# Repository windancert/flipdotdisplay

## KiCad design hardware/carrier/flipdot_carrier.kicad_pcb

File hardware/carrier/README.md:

# Flipdot S3 Pico driver, rev A

A two-layer board that replaces the breadboard: it holds the Waveshare ESP32-S3-Pico in
sockets, the two ribbon headers, the 10k pull-downs, the 20 V / 5 V power stage and a
0.1 ohm resistor for measuring the coil current on a scope. The
circuit is the bench wiring from `firmware/README.md` plus the module power plan in
`CLAUDE.md`, so the firmware does not change. Everything is through-hole and can be
soldered by hand. Board size 111 x 85 mm, four M3 holes.

Layout: ribbon B (COL-SEL4-7) on the left edge and ribbon A (COL-SEL0-3) on the right,
matching where each chain starts on the display: the top row's chain starts at its left
end, and the bottom row is rotated, so its chain starts at the right end. The S3 Pico sits
upright in the middle, USB towards the top edge, antenna at the bottom edge pointing away
from the panels. The pull-downs are between the left header and the S3 Pico, the power stage
below the shared lines on the right, with the 20 V screw terminal on the bottom edge.

Status: designed and checked by KiCad (ERC and DRC clean, the board matches the
schematic), **not yet ordered or built**.

## Files

| File | What |
|------|------|
| `flipdot_carrier.kicad_pro` | open this in KiCad 10 |
| `flipdot_carrier.kicad_sch` | schematic |
| `flipdot_carrier.kicad_pcb` | board, placed and routed |
| `flipdot_carrier_schematic.pdf`, `flipdot_carrier_layout.pdf` | for viewing without KiCad |
| `flipdot_carrier_gerbers.zip` | the file a board maker needs |
| `flipdot.kicad_sym` | project symbols: the ESP32-S3-Pico and a +20V power symbol |
| `tools/` | the generator that makes all of the above (see the end) |

## Parts

| Ref | Qty | Part | Notes |
|-----|-----|------|-------|
| U1 | 1 | Waveshare ESP32-S3-Pico | plugs in, not soldered |
| - | 2 | 1x20 female header, 2.54 mm | the S3 Pico's socket |
| - | 2 | 1x20 male pin header, 2.54 mm | soldered to the S3 Pico, if it has none |
| J1, J2 | 2 | 2x13 shrouded box header, 2.54 mm, straight | ribbon A (COL-SEL0-3), ribbon B (COL-SEL4-7) |
| J3 | 1 | 2-pole screw terminal, 5.08 mm pitch | 20 V in, from the PD trigger module |
| U2 | 1 | Recom R-78E5.0-1.0 | 5 V buck, SIP-3 |
| D1 | 1 | P6KE30CA, DO-15 (Reichelt P6KE 30CA) | bidirectional TVS, 25.6 V standoff, clamps ~41 V; fits either way round |
| D2, D3 | 2 | 1N5819, DO-41 | Schottky; replace the SS34 and SS14 of the module plan |
| C1 | 1 | 470 uF, 35 V or higher, radial, 12.5 mm max diameter, 5 mm lead spacing | coil rail bulk |
| C2 | 1 | 4.7 uF, 50 V, radial, 5 mm diameter, 2 mm lead spacing | buck input |
| C3 | 1 | 100 uF, 16 V, radial, 6.3 mm diameter, 2.5 mm lead spacing | buck output (keep under 220 uF) |
| C4, C5 | 2 | 100 nF ceramic, 5 mm lead spacing | 3.3 V decoupling at each ribbon header |
| R1-R10 | 10 | 10k, 1/4 W | pull-downs: R1-R8 on COL-SEL0-7, R9 ROW-HIGH, R10 ROW-LOW |
| R11 | 1 | 0.1 ohm, 10%, 2 W wirewound, Vitrohm BW235 (Reichelt 2W DRAHT 0,1), body 14.3 x 5.7 mm, 20.32 mm lead spacing | coil current sense; a wire link if not wanted |
| TP1-TP15 | 15 | Keystone 5000-series miniature test point: 3x 5000 red, 2x 5001 black, 4x 5003 orange, 6x 5004 yellow | suggested: red 20V/I+/I-, black GND, orange VIN/5V/VSYS/3V3, yellow signals |
| - | 1 | Joy-IT COM-ZY12PDN-ST (Reichelt DEBO USB-PD 1) | off the board, two wires to J3 |

## Before ordering

1. **S3 Pico row spacing.** Confirmed: the Waveshare board's pin rows measure 17.8 mm
   apart, matching the Raspberry Pi Pico footprint (17.78 mm), pin 1 next to USB.
2. **Antenna end.** Confirmed: the S3 Pico's antenna is on the short edge opposite USB,
   between the pins for GPIO39/40 and GPIO41/42. That end sits at the board's bottom
   edge (marked ANTENNA END). From the GPIO38 pin down to the board edge, across the
   S3 Pico's width plus a margin, there is no ground fill and no vias on either layer; the
   only copper is the four signal pins there and the tracks that reach them from the
   sides. The S3 Pico's GND pin 18 is left unconnected for the same reason.
3. **Ribbon pin 1.** The triangle on the silkscreen next to each header marks pin 1.
   Pin 1 is GND, pin 26 is 20 V. With the ribbons crimped as on the bench (pin 1 to
   pin 1), the red stripe goes on the triangle side.

## Test points

Labelled loops for a meter probe or a scope clip:

| Where | Test points |
|-------|-------------|
| top edge, left of the USB plug | R-HI, R-LO (the two strobes), ROW4, COL4 (top address bits), SEL0, SEL4 (first panel on each ribbon) |
| top edge, right of the USB plug | 3V3, GND |
| power corner, bottom right | 20V, VIN, 5V, VSYS, GND, top to bottom in the order the power flows |
| above R11, which sits above D1 | I+, I- (coil current) |

VIN is the buck's input, behind D2. If 5V reads 0 V with 20V present, VIN tells the
cases apart: about 0 V means D2 is in backwards or C2 is shorted; about 19.5 V means
the R-78E itself.

The strobes are the ones to watch on a scope: each pulse should be about 260 us, never
more than the firmware's 400 us ceiling.

**Coil current.** The coils get their 20 V through R11 (0.1 ohm), which sits behind C1 so
it carries the pulses themselves. Probe I+ on one channel and I- on another, both ground
clips on GND, both channels AC-coupled at about 20 mV/div, and show CH1 - CH2: 100 mV is
1 A, so a 0.74 A pulse reads about 74 mV. Trigger on R-HI or R-LO with a third channel.
R11 takes about 0.6 % off the coil current (0.1 ohm against the coil's 16 ohm).

I+ is tapped straight off R11's pad. Ribbon A's current also leaves R11 straight from its
pad, but ribbon B's runs past the I- test point first, through about 4.5 mm of track, so
pulses on the top row (ribbon B) read about 3 % high.

R11 is only good to 10 %, so measure its real value once, before the S3 Pico goes in and
with no ribbons connected: set the bench supply to about 1 V with a 0.5 A current limit,
connect + to I- and - to I+ (at that voltage the current can only flow through R11),
read the current on the supply and the millivolts between I+ and I- on a multimeter, and
divide. Use that value instead of 0.1 ohm when converting scope readings to amps.

## Ordering

Planned maker: **Aisler** (Germany), 2-layer standard boards. Aisler reads KiCad files
directly: upload `flipdot_carrier.kicad_pcb` (or `flipdot_carrier_gerbers.zip`) and check
its preview of both sides. The tightest rules used are 0.2 mm clearance, 0.3 mm tracks
and 0.3 mm via holes, within every maker's standard process. Parts from Reichelt.

Order only after the 20 V charger test (see CLAUDE.md, Power): if the charger does not
settle on 20 V with ~490 uF on the module's output, the board needs a coil-rail switch.
**Result: it depends on the charger.** One charger failed about half the time with
470 uF directly on the module's output, another passed every time (see CLAUDE.md).
**Open item:** the switched coil rail (version 2 of the power page) is postponed, not
dropped; this board has no switch yet. Decide before ordering.

## Assembly

Solder the lowest parts first so the board lies flat on the bench:

1. R1-R10 (either way round).
2. D2, D3: the band is the cathode, the silkscreen marks it with a K. D1 (bidirectional)
   goes either way round.
3. C4, C5 (either way round), R11 (either way round), and the 15 test point loops
   TP1-TP15 (either way round; the colours suggested in the parts list).
4. The two 1x20 female headers for the S3 Pico. Plug the S3 Pico into them first so they line
   up, then solder.
5. J1, J2: the notch in the shroud goes on the side the silkscreen outline shows.
6. C1, C2, C3: the long leg is +, the stripe on the can is -, the silkscreen marks +.
7. U2: pin 1 (+Vin, marked on the module) in the leftmost hole, the body over its
   silkscreen outline.
8. J3: the wire openings face the bottom edge.

## First power-up

With the S3 Pico **out** of its socket and no ribbons connected:

1. Set the PD trigger to 20 V (LED dark blue) and connect it to J3: + on the left,
   - on the right, as marked.
2. Measure against a GND test point:
   - 20V test point, J1 pin 26 and J2 pin 26: about 20 V.
   - VIN test point: about 19.5 V (20 V minus D2).
   - 5V test point: about 5 V.
   - VSYS test point (also socket pin 39, right-hand row, second from the top):
     about 4.7 V (5 V minus the diode). **If this reads 20 V, stop.**
   - Every other socket pin: 0 V.
3. Unplug, insert the S3 Pico (USB towards the top edge), power up again. The
   status LED should go blue, then yellow and green as on the bench. The 3V3 test
   point should now read about 3.3 V.
4. Unpower, then connect one ribbon between the board and a panel and check its
   orientation with a continuity meter, still unpowered: J3 - to the panel's ground
   plane (or its ribbon pin 1 or 2) must beep, J3 + to the panel's ground must not.
   A plug the wrong way round puts 20 V on the panel's ground pins. Repeat for the
   other ribbon, then power up.

## Regenerating

The schematic and board are generated by `tools/` and can be rebuilt with:

```sh
python tools/build.py
```

It needs KiCad 10 installed at its default path. It regenerates the schematic, runs ERC,
places and routes the board (about a minute and a half), runs DRC, and writes the
Gerbers and PDFs.

- `tools/design.py` holds the parts, their connections and their positions on the board.
- `tools/gen_sch.py` writes the schematic, `tools/gen_pcb.py` the board, using
  `tools/router.py`, a small autorouter.
- `tools/render.py out.png` draws the copper to a PNG for a quick look.

A rebuild overwrites the `.kicad_pcb`. To edit the board by hand in KiCad, do that from
then on and stop using `build.py` for the board; `python tools/build.py --no-pcb` still
rebuilds only the schematic.

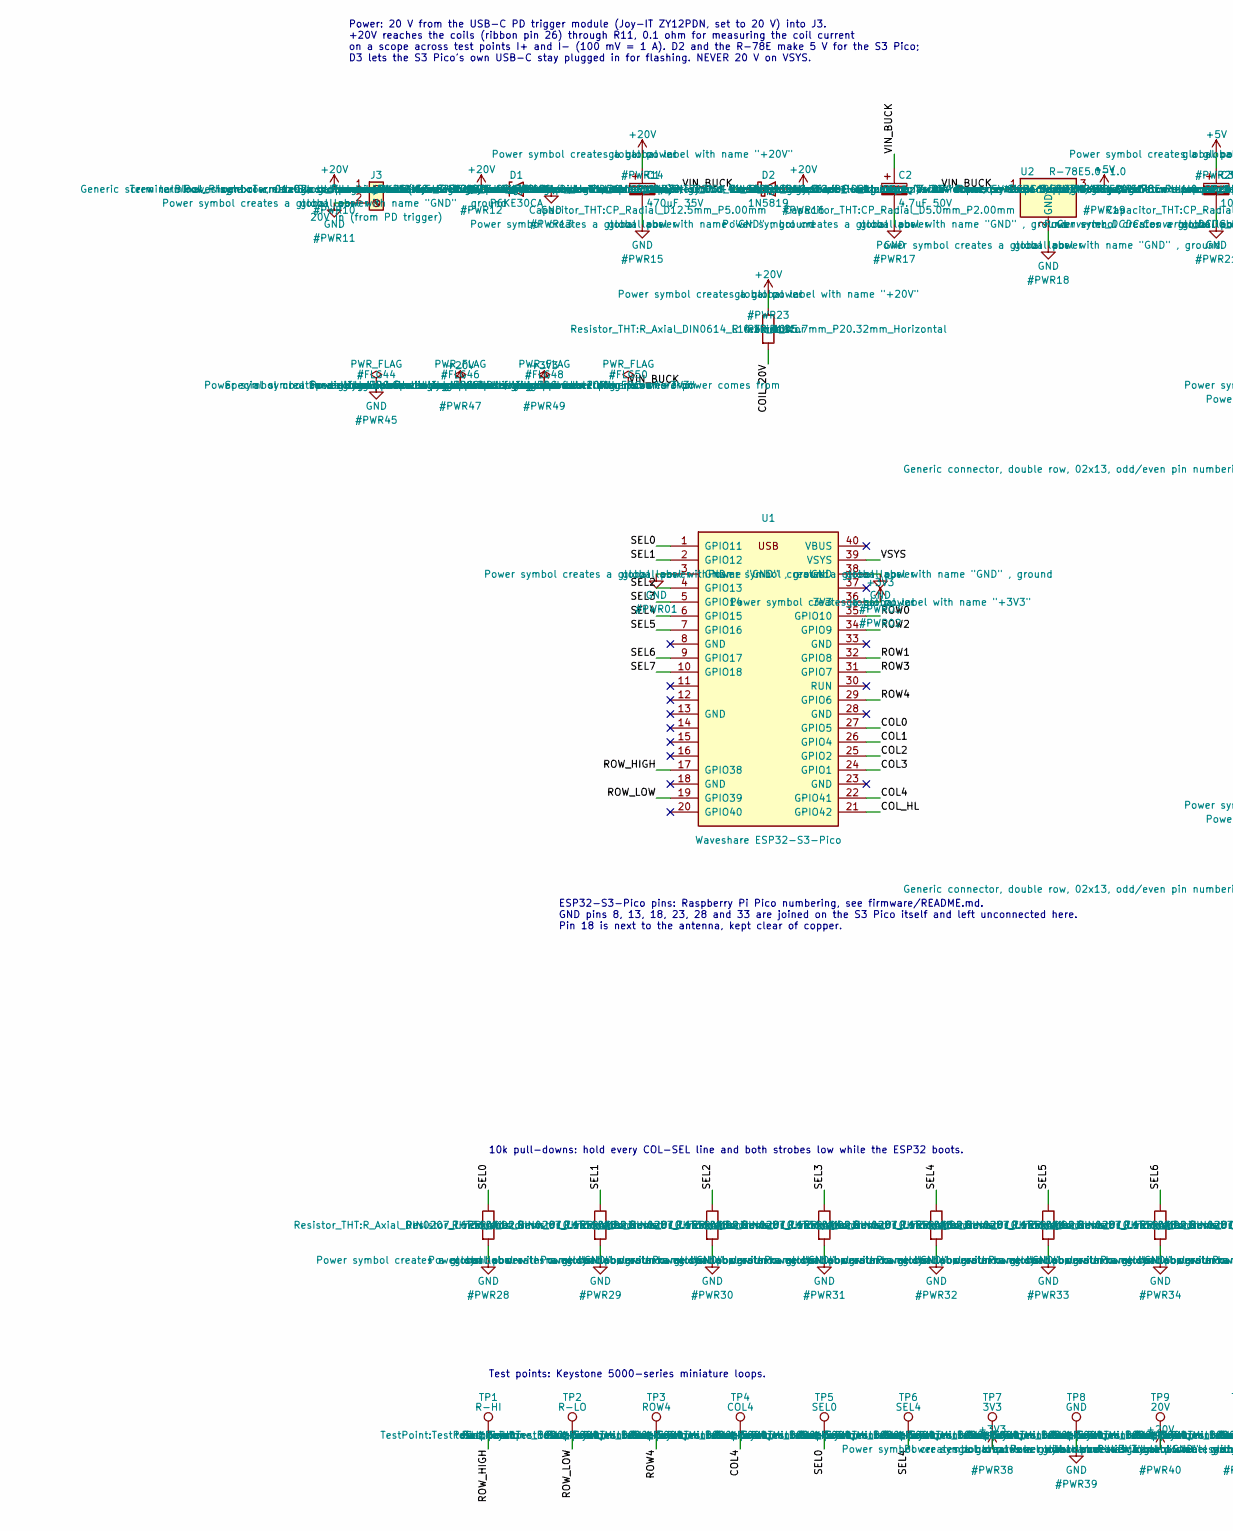
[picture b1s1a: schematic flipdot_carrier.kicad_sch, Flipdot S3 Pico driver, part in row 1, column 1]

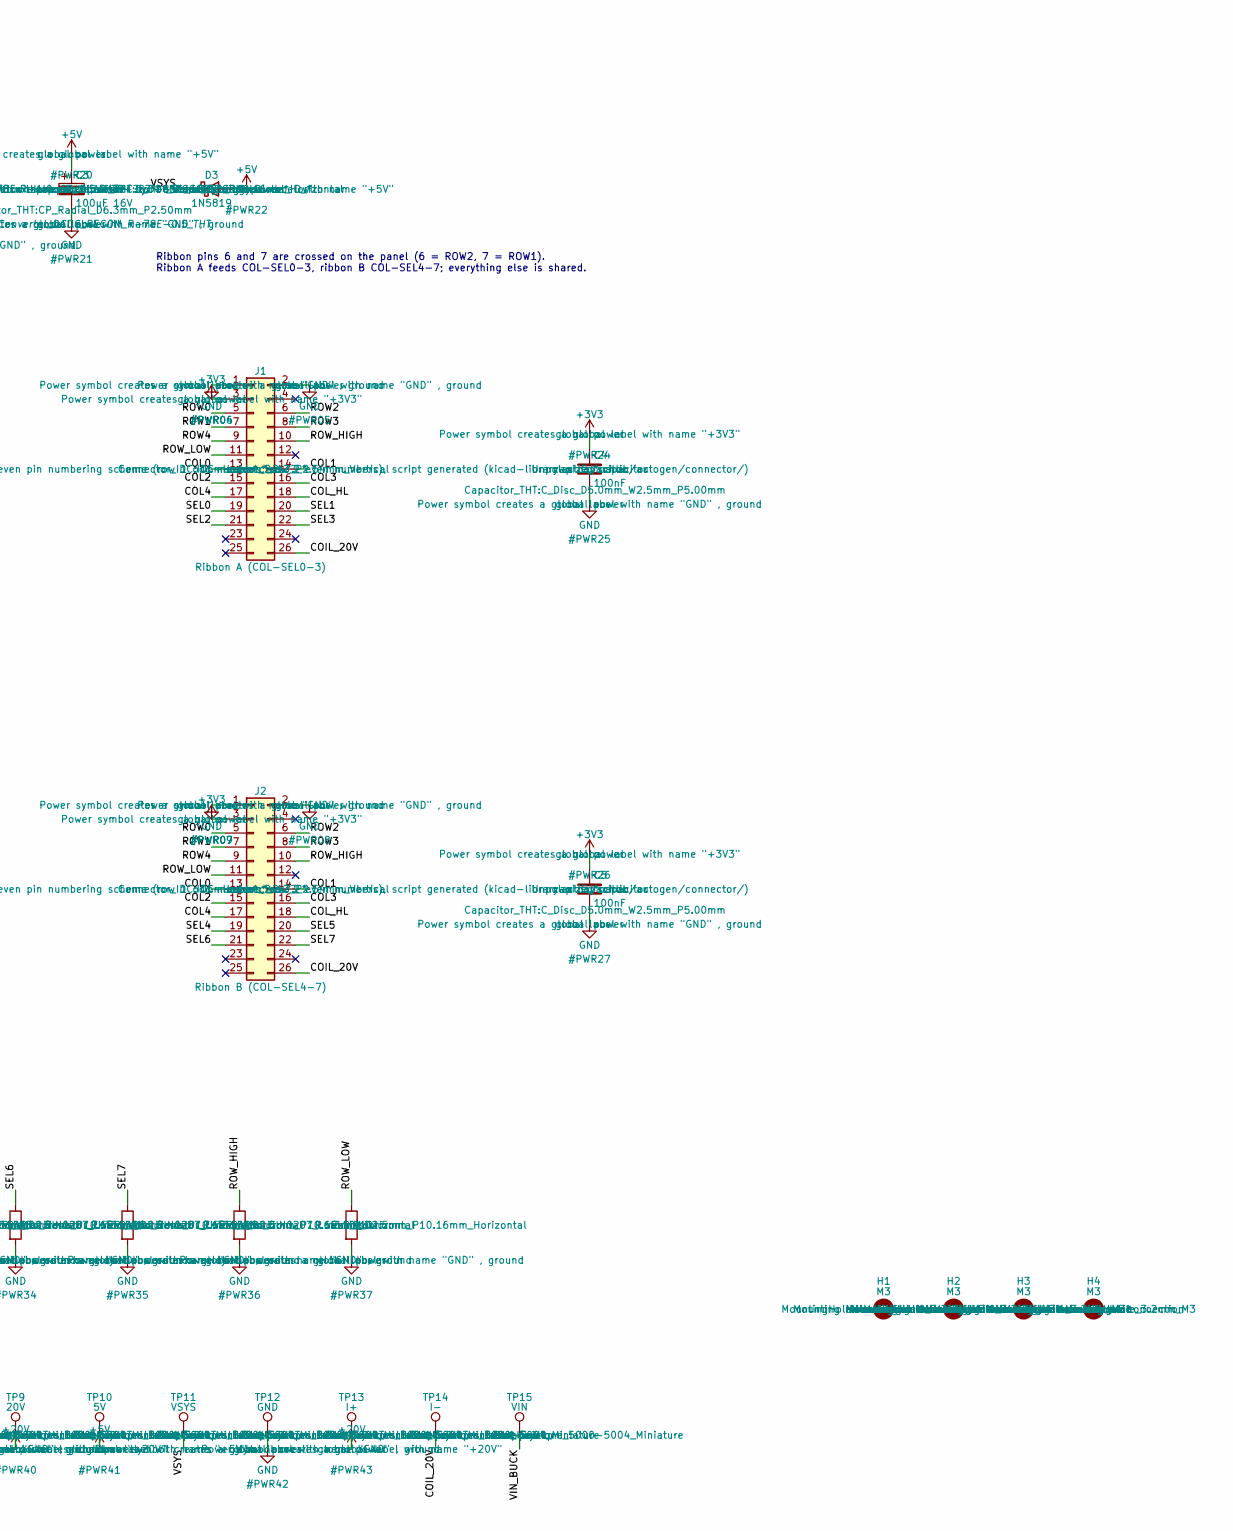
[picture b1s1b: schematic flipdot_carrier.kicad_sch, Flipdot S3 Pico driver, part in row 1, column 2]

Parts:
C1: 470uF 35V; CP_Radial_D12.5mm_P5.00mm
C2: 4.7uF 50V; CP_Radial_D5.0mm_P2.00mm
C3: 100uF 16V; CP_Radial_D6.3mm_P2.50mm
C4, C5: 100nF; C_Disc_D5.0mm_W2.5mm_P5.00mm
D1: P6KE30CA; D_DO-15_P10.16mm_Horizontal
D2, D3: 1N5819; D_DO-41_SOD81_P10.16mm_Horizontal
H1, H2, H3, H4: M3; MountingHole_3.2mm_M3
J1: Ribbon A (COL-SEL0-3); IDC-Header_2x13_P2.54mm_Vertical
J2: Ribbon B (COL-SEL4-7); IDC-Header_2x13_P2.54mm_Vertical
J3: 20V in (from PD trigger); TerminalBlock_Phoenix_MKDS-1,5-2-5.08_1x02_P5.08mm_Horizont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
R1, R2, R3, R4, R5, R6, R7, R8, R9, R10: 10k; R_Axial_DIN0207_L6.3mm_D2.5mm_P10.16mm_Horizontal
R11: 0.1R 10%; R_Axial_DIN0614_L14.3mm_D5.7mm_P20.32mm_Horizontal
TP1: R-HI; TestPoint_Keystone_5000-5004_Miniature
TP2: R-LO; TestPoint_Keystone_5000-5004_Miniature
TP3: ROW4; TestPoint_Keystone_5000-5004_Miniature
TP4: COL4; TestPoint_Keystone_5000-5004_Miniature
TP5: SEL0; TestPoint_Keystone_5000-5004_Miniature
TP6: SEL4; TestPoint_Keystone_5000-5004_Miniature
TP7: 3V3; TestPoint_Keystone_5000-5004_Miniature
TP8, TP12: GND; TestPoint_Keystone_5000-5004_Miniature
TP9: 20V; TestPoint_Keystone_5000-5004_Miniature
TP10: 5V; TestPoint_Keystone_5000-5004_Miniature
TP11: VSYS; TestPoint_Keystone_5000-5004_Miniature
TP13: I+; TestPoint_Keystone_5000-5004_Miniature
TP14: I-; TestPoint_Keystone_5000-5004_Miniature
TP15: VIN; TestPoint_Keystone_5000-5004_Miniature
U1: Waveshare ESP32-S3-Pico; RaspberryPi_Pico_Common_THT
U2: R-78E5.0-1.0; Converter_DCDC_RECOM_R-78E-0.5_THT

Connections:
+3V3: C4.1, C5.1, J1.3, J2.3, TP7.1, U1.36 (3V3)
+5V: C3.1, D3.2 (A), TP10.1, U2.3 (OUT)
+20V: C1.1, D1.1 (K), D2.2 (A), J3.1, R11.1, TP9.1, TP13.1
/COIL_20V: J1.26, J2.26, R11.2, TP14.1
/COL0: J1.13, J2.13, U1.27 (GPIO5)
/COL1: J1.14, J2.14, U1.26 (GPIO4)
/COL2: J1.15, J2.15, U1.25 (GPIO2)
/COL3: J1.16, J2.16, U1.24 (GPIO1)
/COL4: J1.17, J2.17, TP4.1, U1.22 (GPIO41)
/COL_HL: J1.18, J2.18, U1.21 (GPIO42)
/ROW0: J1.5, J2.5, U1.35 (GPIO10)
/ROW1: J1.7, J2.7, U1.32 (GPIO8)
/ROW2: J1.6, J2.6, U1.34 (GPIO9)
/ROW3: J1.8, J2.8, U1.31 (GPIO7)
/ROW4: J1.9, J2.9, TP3.1, U1.29 (GPIO6)
/ROW_HIGH: J1.10, J2.10, R9.1, TP1.1, U1.17 (GPIO38)
/ROW_LOW: J1.11, J2.11, R10.1, TP2.1, U1.19 (GPIO39)
/SEL0: J1.19, R1.1, TP5.1, U1.1 (GPIO11)
/SEL1: J1.20, R2.1, U1.2 (GPIO12)
/SEL2: J1.21, R3.1, U1.4 (GPIO13)
/SEL3: J1.22, R4.1, U1.5 (GPIO14)
/SEL4: J2.19, R5.1, TP6.1, U1.6 (GPIO15)
/SEL5: J2.20, R6.1, U1.7 (GPIO16)
/SEL6: J2.21, R7.1, U1.9 (GPIO17)
/SEL7: J2.22, R8.1, U1.10 (GPIO18)
/VIN_BUCK: C2.1, D2.1 (K), TP15.1, U2.1 (IN)
/VSYS: D3.1 (K), TP11.1, U1.39 (VSYS)
GND: C1.2, C2.2, C3.2, C4.2, C5.2, D1.2 (A), J1.1, J1.2, J2.1, J2.2, J3.2, R1.2, R2.2, R3.2, R4.2, R5.2, R6.2, R7.2, R8.2, R9.2, R10.2, TP8.1, TP12.1, U1.3 (GND), U1.38 (GND), U2.2 (GND)

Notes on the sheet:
Power: 20 V from the USB-C PD trigger module (Joy-IT ZY12PDN, set to 20 V) into J3. +20V reaches the coils (ribbon pin 26) through R11, 0.1 ohm for measuring the coil current on a scope across test points I+ and I- (100 mV = 1 A). D2 and the R-78E make 5 V for the S3 Pico; D3 lets the S3 Pico's own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
ESP32-S3-Pico pins: Raspberry Pi Pico numbering, see firmware/README.md. GND pins 8, 13, 18, 23, 28 and 33 are joined on the S3 Pico itself and left unconnected here. Pin 18 is next to the antenna, kept clear of copper.
Test points: Keystone 5000-series miniature loops.
10k pull-downs: hold every COL-SEL line and both strobes low while the ESP32 boots.
Ribbon pins 6 and 7 are crossed on the panel (6 = ROW2, 7 = ROW1). Ribbon A feeds COL-SEL0-3, ribbon B COL-SEL4-7; everything else is shared.

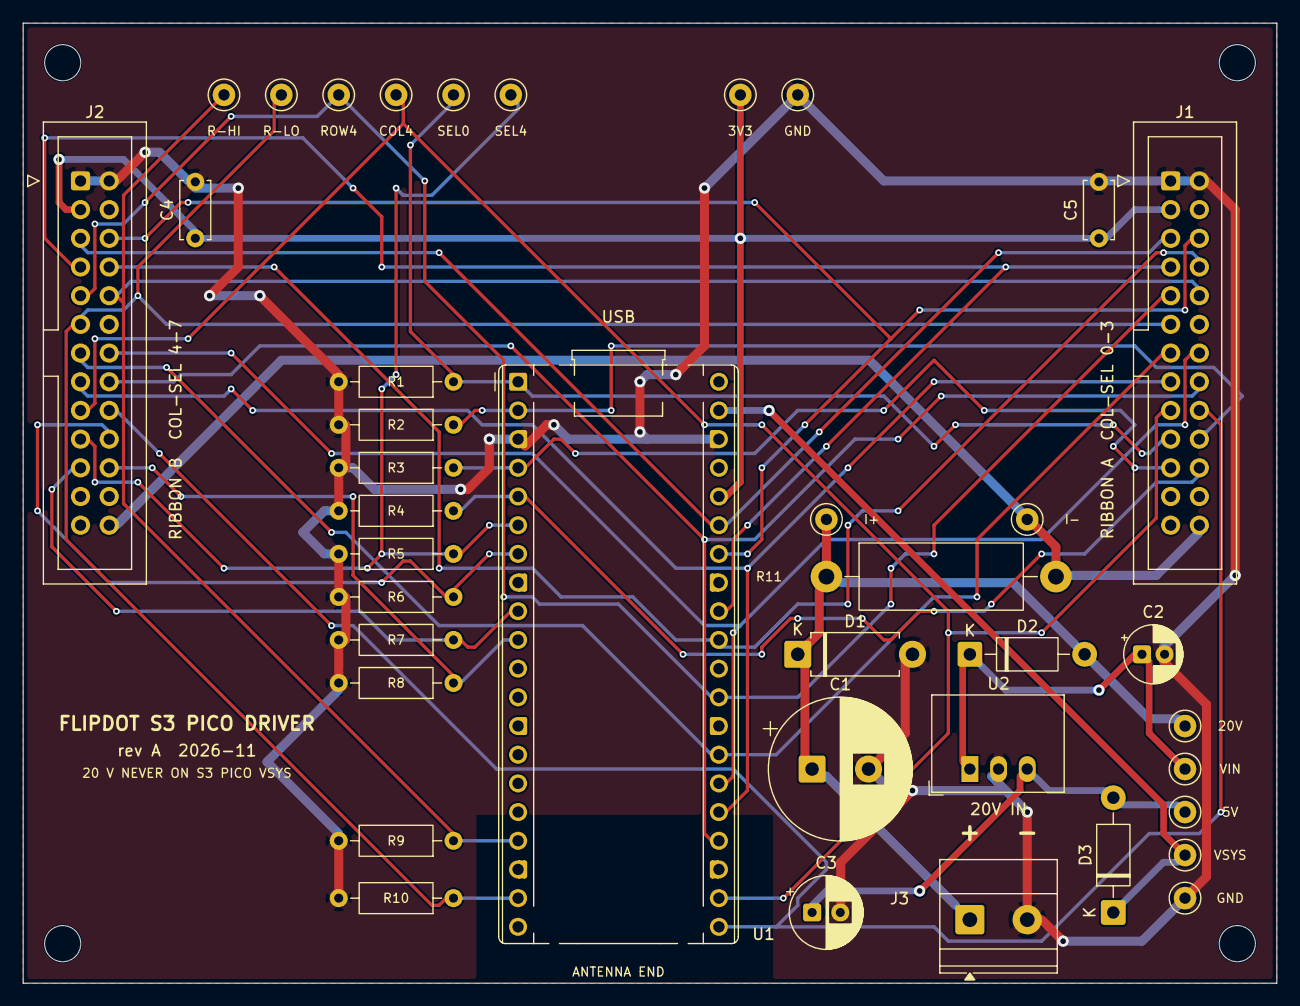
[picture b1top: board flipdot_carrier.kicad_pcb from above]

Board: 2 copper layers, 111.0 x 85.0 mm, 43 parts (0 on the bottom side), 28 nets.

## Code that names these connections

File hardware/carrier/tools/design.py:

"""The carrier board's parts and connections, shared by gen_sch.py and gen_pcb.py.

Board coordinates are millimetres from the board's top-left corner, y down,
seen from the component side.
"""
import sys

# Ribbon pins 5-18 are the same on both ribbons. Ribbon pins 6 and 7 are crossed on
# the panel (6 = ROW2, 7 = ROW1); the GPIOs run straight and the firmware undoes it.
SHARED = {
    5: "ROW0", 6: "ROW2", 7: "ROW1", 8: "ROW3", 9: "ROW4",
    10: "ROW_HIGH", 11: "ROW_LOW",
    13: "COL0", 14: "COL1", 15: "COL2", 16: "COL3", 17: "COL4", 18: "COL_HL",
}


def ribbon(sels):
    # The coils get their 20 V through the current-sense resistor R11.
    m = {1: "GND", 2: "GND", 3: "+3V3", 26: "COIL_20V"}
    m.update(SHARED)
    for i, s in enumerate(sels):
        m[19 + i] = s
    return m


# Waveshare ESP32-S3-Pico header pins (Raspberry Pi Pico numbering), from
# firmware/README.md and firmware/main/panel_hw.c. The S3 Pico's other GND pins
# (8, 13, 18, 23, 28, 33) are joined on the S3 Pico itself and left unconnected here;
# pin 18 sits next to the antenna, which wants as little copper around it as possible.
PICO = {
    1: "SEL0", 2: "SEL1", 3: "GND", 4: "SEL2", 5: "SEL3", 6: "SEL4", 7: "SEL5",
    9: "SEL6", 10: "SEL7", 17: "ROW_HIGH", 19: "ROW_LOW",
    21: "COL_HL", 22: "COL4", 24: "COL3", 25: "COL2", 26: "COL1", 27: "COL0",
    29: "ROW4", 31: "ROW3", 32: "ROW1", 34: "ROW2", 35: "ROW0",
    36: "+3V3", 38: "GND", 39: "VSYS",
}

PICO_PIN_NAMES = {
    1: "GPIO11", 2: "GPIO12", 3: "GND", 4: "GPIO13", 5: "GPIO14", 6: "GPIO15",
    7: "GPIO16", 8: "GND", 9: "GPIO17", 10: "GPIO18", 13: "GND", 17: "GPIO38",
    18: "GND", 19: "GPIO39", 20: "GPIO40", 21: "GPIO42", 22: "GPIO41", 23: "GND", 24: "GPIO1",
    25: "GPIO2", 26: "GPIO4", 27: "GPIO5", 28: "GND", 29: "GPIO6", 30: "RUN",
    31: "GPIO7", 32: "GPIO8", 33: "GND", 34: "GPIO9", 35: "GPIO10", 36: "3V3",
    38: "GND", 39: "VSYS", 40: "VBUS",
}

POWER_NETS = {"GND", "+3V3", "+5V", "+20V"}  # drawn with power symbols

# KiCad 10's own libraries, at its default install path.
if sys.platform == "darwin":
    KICAD_SHARE = "/Applications/KiCad/KiCad.app/Contents/SharedSupport"
else:
    KICAD_SHARE = "C:/Program Files/KiCad/10.0/share/kicad"
FP = f"{KICAD_SHARE}/footprints"

# ref, symbol, value, footprint, {pin: net}, schematic (x, y), board (x, y, rot), extra fields
PARTS = [
    ("U1", "flipdot:ESP32-S3-Pico", "Waveshare ESP32-S3-Pico",
     "Module:RaspberryPi_Pico_Common_THT", PICO, (101.6, 139.7), (43.82, 31.75, 0),
     {"Note": "Plugged into 2x 1x20 female headers, not soldered"}),
    ("J1", "Connector_Generic:Conn_02x13_Odd_Even", "Ribbon A (COL-SEL0-3)",
     "Connector_IDC:IDC-Header_2x13_P2.54mm_Vertical", ribbon(["SEL0", "SEL1", "SEL2", "SEL3"]),
     (215.9, 101.6), (101.6, 13.97, 0), {}),
    ("J2", "Connector_Generic:Conn_02x13_Odd_Even", "Ribbon B (COL-SEL4-7)",
     "Connector_IDC:IDC-Header_2x13_P2.54mm_Vertical", ribbon(["SEL4", "SEL5", "SEL6", "SEL7"]),
     (215.9, 177.8), (5.08, 13.97, 0), {}),
    ("J3", "Connector:Screw_Terminal_01x02", "20V in (from PD trigger)",
     "TerminalBlock_Phoenix:TerminalBlock_Phoenix_MKDS-1,5-2-5.08_1x02_P5.08mm_Horizontal",
     {1: "+20V", 2: "GND"}, (30.48, 50.8), (83.82, 79.375, 0), {}),
    ("D1", "Device:D_Zener", "P6KE30CA", "Diode_THT:D_DO-15_P10.16mm_Horizontal",
     {1: "+20V", 2: "GND"}, (55.88, 50.8), (68.58, 55.88, 0),
     {"Note": "Bidirectional TVS, 25.6 V standoff, either way round (Reichelt P6KE 30CA)"}),
    ("C1", "Device:C_Polarized", "470uF 35V", "Capacitor_THT:CP_Radial_D12.5mm_P5.00mm",
     {1: "+20V", 2: "GND"}, (78.74, 50.8), (69.85, 66.04, 0), {}),
    ("D2", "Device:D_Schottky", "1N5819", "Diode_THT:D_DO-41_SOD81_P10.16mm_Horizontal",
     {1: "VIN_BUCK", 2: "+20V"}, (101.6, 50.8), (83.82, 55.88, 0), {}),
    ("C2", "Device:C_Polarized", "4.7uF 50V", "Capacitor_THT:CP_Radial_D5.0mm_P2.00mm",
     {1: "VIN_BUCK", 2: "GND"}, (124.46, 50.8), (99.06, 55.88, 0), {}),
    ("U2", "Converter_DCDC:R-78E5.0-1.0", "R-78E5.0-1.0",
     "Converter_DCDC:Converter_DCDC_RECOM_R-78E-0.5_THT",
     {1: "VIN_BUCK", 2: "GND", 3: "+5V"}, (152.4, 50.8), (83.82, 66.04, 0), {}),
    ("C3", "Device:C_Polarized", "100uF 16V", "Capacitor_THT:CP_Radial_D6.3mm_P2.50mm",
     {1: "+5V", 2: "GND"}, (182.88, 50.8), (69.85, 78.74, 0), {}),
    ("D3", "Device:D_Schottky", "1N5819", "Diode_THT:D_DO-41_SOD81_P10.16mm_Horizontal",
     {1: "VSYS", 2: "+5V"}, (208.28, 50.8), (96.52, 78.74, 90), {}),
    # Current sense for the coils: 0.1 ohm behind C1, so it carries the coil pulses
    # themselves. Scope across the I+ and I- test points: 100 mV is 1 A.
    ("R11", "Device:R", "0.1R 10%", "Resistor_THT:R_Axial_DIN0614_L14.3mm_D5.7mm_P20.32mm_Horizontal",
     {1: "+20V", 2: "COIL_20V"}, (101.6, 76.2), (71.12, 49.0, 0),
     {"Note": "Vitrohm BW235, 0.1 ohm 10%, 2 W wirewound (Reichelt 2W DRAHT 0,1); "
              "a wire link if no current sense is wanted"}),
    ("C4", "Device:C", "100nF", "Capacitor_THT:C_Disc_D5.0mm_W2.5mm_P5.00mm",
     {1: "+3V3", 2: "GND"}, (276.86, 101.6), (15.24, 19.05, 90), {}),
    ("C5", "Device:C", "100nF", "Capacitor_THT:C_Disc_D5.0mm_W2.5mm_P5.00mm",
     {1: "+3V3", 2: "GND"}, (276.86, 177.8), (95.25, 19.05, 90), {}),
]

# Each pull-down level with its S3 Pico pin where there is room (3.81 mm apart).
PULLDOWN_Y = [31.75 + 3.81 * i for i in range(8)] + [72.39, 77.47]
PULLDOWNS = ["SEL0", "SEL1", "SEL2", "SEL3", "SEL4", "SEL5", "SEL6", "SEL7", "ROW_HIGH", "ROW_LOW"]
for i, net in enumerate(PULLDOWNS):
    PARTS.append((f"R{i + 1}", "Device:R", "10k",
                  "Resistor_THT:R_Axial_DIN0207_L6.3mm_D2.5mm_P10.16mm_Horizontal",
                  {1: net, 2: "GND"}, (50.8 + i * 20.32, 238.76),
                  (38.1, PULLDOWN_Y[i], 180), {}))

# Test points (Keystone 5000-series miniature loops): net, silkscreen label, board x, y.
# Signals along the top edge left of the USB plug; 3.3 V and a GND right of it; 20 V,
# the buck input, 5 V, VSYS and a second GND in the power corner, in the order the
# power flows. VIN tells a reversed D2 or a shorted C2 from a dead buck.
TESTPOINTS = [
    ("ROW_HIGH", "R-HI", 17.78, 6.35), ("ROW_LOW", "R-LO", 22.86, 6.35),
    ("ROW4", "ROW4", 27.94, 6.35), ("COL4", "COL4", 33.02, 6.35),
    ("SEL0", "SEL0", 38.1, 6.35), ("SEL4", "SEL4", 43.18, 6.35),
    ("+3V3", "3V3", 63.5, 6.35), ("GND", "GND", 68.58, 6.35),
    ("+20V", "20V", 102.87, 62.23), ("+5V", "5V", 102.87, 69.85),
    ("VSYS", "VSYS", 102.87, 73.66), ("GND", "GND", 102.87, 77.47),
    ("+20V", "I+", 71.12, 43.94), ("COIL_20V", "I-", 88.9, 43.94),
    ("VIN_BUCK", "VIN", 102.87, 66.04),
]
for i, (net, label, x, y) in enumerate(TESTPOINTS):
    PARTS.append((f"TP{i + 1}", "Connector:TestPoint", label,
                  "TestPoint:TestPoint_Keystone_5000-5004_Miniature", {1: net},
                  (50.8 + i * 15.24, 276.86), (x, y, 0), {}))

BOARD_W, BOARD_H = 111.0, 85.0
# The S3 Pico's antenna is on the short edge opposite USB, between the GPIO39/40 and
# GPIO41/42 pins, at the board's bottom edge. From the GPIO38 pin to the board edge,
# across the S3 Pico plus a margin: no copper fill and no vias, and tracks only where
# they have to reach a pin.
ANTENNA_AREA = (40.0, 70.0, 66.5, 85.0)
HOLES = [(3.5, 3.5), (107.5, 3.5), (3.5, 81.5), (107.5, 81.5)]
for i in range(4):
    PARTS.append((f"H{i + 1}", "Mechanical:MountingHole", "M3",
                  "MountingHole:MountingHole_3.2mm_M3", {}, (330.2 + i * 12.7, 254.0),
                  HOLES[i] + (0,), {}))

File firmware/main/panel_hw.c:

// Panels wired straight to the GPIOs of a Waveshare ESP32-S3-Pico. The bits of a
// shift_frame_t are fanned out to the GPIOs and the active polarity strobe is
// pulsed by the RMT.
//
// Address, polarity and strobe lines are shared by every panel. With more than one
// ribbon, each shared GPIO goes to the same pin on every ribbon; only the COL-SEL
// lines are per panel. COL-SEL0-3 are pins 19-22 of ribbon A (top row), COL-SEL4-7
// pins 19-22 of ribbon B (bottom row). Ribbon pins in brackets below.
//
// ROW0-4 are wired straight to ribbon pins 5-9; the panel's 6<->7 row crossing is
// undone in firmware (ROW_BIT). COL-SEL and strobe lines need external 10k
// pull-downs, since they float until panel_hw_init runs.
//
// Both polarity strobes share ONE RMT channel: its output is re-pointed to ROW-HIGH
// or ROW-LOW through the GPIO matrix per pulse, and the idle polarity pin is driven
// low as a plain GPIO, so only one strobe is ever live.

#include "panel_hw.h"

#include "driver/gpio.h"
#include "driver/rmt_tx.h"
#include "esp_check.h"
#include "esp_log.h"
#include "esp_rom_gpio.h"
#include "esp_rom_sys.h"
#include "esp_timer.h"
#include "flipdot_map.h"
#include "freertos/FreeRTOS.h"
#include "sdkconfig.h"
#include "soc/gpio_sig_map.h"  // SIG_GPIO_OUT_IDX
#include "soc/gpio_struct.h"   // read back the RMT output signal from the matrix

#if !CONFIG_IDF_TARGET_ESP32S3
#error "The pin map is for the Waveshare ESP32-S3-Pico"
#endif

// Waveshare ESP32-S3-Pico, two ribbons, room for all eight panels. Header pins only,
// avoiding GPIO33-37, which Waveshare lists for PSRAM. Each group is an unbroken run
// down the header, apart from GND and RUN pins; S3 Pico header pins in parentheses.
// Seen from above with USB at the top (pin 1 top left).
// Right header, top to bottom: ROW0-4, COL0-4, COL-H/L, in the ribbon's own order.
static const gpio_num_t ROW_PINS[5] = {GPIO_NUM_10, GPIO_NUM_9, GPIO_NUM_8, GPIO_NUM_7, GPIO_NUM_6};  // (35-29)
static const gpio_num_t COL_PINS[5] = {GPIO_NUM_5, GPIO_NUM_4, GPIO_NUM_2, GPIO_NUM_1, GPIO_NUM_41};  // (27-22)
#define PIN_COL_HL GPIO_NUM_42  // [18] (21)
// Left header: COL-SEL0-7 at the top, the strobes at the bottom.
static const gpio_num_t SEL_PINS[8] = {
    GPIO_NUM_11, GPIO_NUM_12, GPIO_NUM_13, GPIO_NUM_14,  // ribbon A [19-22] (1-5)
    GPIO_NUM_15, GPIO_NUM_16, GPIO_NUM_17, GPIO_NUM_18,  // ribbon B [19-22] (6-10)
};
#define PIN_ROW_HIGH GPIO_NUM_38  // [10] (17)
#define PIN_ROW_LOW GPIO_NUM_39   // [11] (19)

// Bit positions within shift_frame_t, matching flipdot_dot_frame(). ROW0-4 are
// u1 bits 0-4, COL0-4 are u2 bits 0-4, COL-SEL0-5 u3 bits 2-7, COL-SEL6-7 u2 bits 5-6.
#define U1_COL_HL_BIT (1u << 5)
#define U3_ROW_HIGH_BIT (1u << 0)
#define U3_ROW_LOW_BIT (1u << 1)

#define RMT_RESOLUTION_HZ (1000 * 1000)
#define RMT_DONE_TIMEOUT_MS 50

// Measured 0.25 A ceiling applies at this dot rate, so never go faster.
#define MIN_PULSE_PERIOD_US 335
// Address lines settle before the strobe; HC decoders need only tens of ns.
#define ADDR_SETTLE_US 2

static const char *TAG = "panel_hw";

static rmt_channel_handle_t s_rmt;
static rmt_encoder_handle_t s_encoder;
static uint32_t s_strobe_sig;             // RMT TX output signal, read from the matrix
static gpio_num_t s_rmt_pin = PIN_ROW_HIGH;  // strobe pin the RMT currently drives
static int64_t s_last_pulse_us;

static bool sel_active(shift_frame_t frame, int sel)
{
    return sel < 6 ? (frame.u3 >> (2 + sel)) & 1 : (frame.u2 >> (5 + sel - 6)) & 1;
}

// Points the single RMT channel at one strobe pin, parking the other as a driven-
// low GPIO, so only the chosen polarity can be energised.
static void route_rmt_to(gpio_num_t pin)
{
    if (pin == s_rmt_pin) {
        return;
    }
    // Park the pin the RMT is leaving: back to plain GPIO, held low.
    esp_rom_gpio_connect_out_signal(s_rmt_pin, SIG_GPIO_OUT_IDX, false, false);
    gpio_set_direction(s_rmt_pin, GPIO_MODE_OUTPUT);
    gpio_set_level(s_rmt_pin, 0);
    // Route the RMT output to the new pin; this also enables its output path.
    esp_rom_gpio_connect_out_signal(pin, s_strobe_sig, false, false);
    s_rmt_pin = pin;
}

void panel_hw_init(void)
{
    // All driven pins start as outputs held low. The external 10k pull-downs on the
    // strobe and select lines cover the window before this runs, while they float.
    uint64_t mask = (1ULL << PIN_COL_HL) | (1ULL << PIN_ROW_HIGH) | (1ULL << PIN_ROW_LOW);
    for (int i = 0; i < 5; i++) {
        mask |= (1ULL << ROW_PINS[i]) | (1ULL << COL_PINS[i]);
    }
    for (int i = 0; i < 8; i++) {
        mask |= 1ULL << SEL_PINS[i];
    }
    const gpio_config_t out_cfg = {.pin_bit_mask = mask, .mode = GPIO_MODE_OUTPUT};
    ESP_ERROR_CHECK(gpio_config(&out_cfg));
    for (int pin = 0; pin < 64; pin++) {
        if (mask & (1ULL << pin)) {
            gpio_set_level(pin, 0);
        }
    }

    // One TX channel, initially bound to ROW-HIGH. Reading the signal it connected
    // back out of the matrix means the reroute never depends on the channel number.
    const rmt_tx_channel_config_t rmt_cfg = {
        .gpio_num = PIN_ROW_HIGH,
        .clk_src = RMT_CLK_SRC_DEFAULT,
        .resolution_hz = RMT_RESOLUTION_HZ,
        .mem_block_symbols = SOC_RMT_MEM_WORDS_PER_CHANNEL,
        .trans_queue_depth = 1,
    };
    ESP_ERROR_CHECK(rmt_new_tx_channel(&rmt_cfg, &s_rmt));
    s_strobe_sig = GPIO.func_out_sel_cfg[PIN_ROW_HIGH].func_sel;
    s_rmt_pin = PIN_ROW_HIGH;

    const rmt_copy_encoder_config_t enc_cfg = {};
    ESP_ERROR_CHECK(rmt_new_copy_encoder(&enc_cfg, &s_encoder));
    ESP_ERROR_CHECK(rmt_enable(s_rmt));
}

// The panel swaps ribbon pins 6 and 7 (pin 6 = ROW2, pin 7 = ROW1). With ROW_PINS[i]
// wired straight to ribbon pin 5 + i, undo that here: ROW_PINS[1] (pin 6) carries
// row address bit 2, ROW_PINS[2] (pin 7) carries bit 1.
static const uint8_t ROW_BIT[5] = {0, 2, 1, 3, 4};

static void set_lines(shift_frame_t frame)
{
    for (int i = 0; i < 5; i++) {
        gpio_set_level(ROW_PINS[i], (frame.u1 >> ROW_BIT[i]) & 1);
        gpio_set_level(COL_PINS[i], (frame.u2 >> i) & 1);
    }
    gpio_set_level(PIN_COL_HL, (frame.u1 & U1_COL_HL_BIT) ? 1 : 0);
    for (int i = 0; i < 8; i++) {
        gpio_set_level(SEL_PINS[i], sel_active(frame, i));
    }
}

static void strobe(uint32_t width_us)
{
    // The RMT ends the pulse itself, so a hung CPU, a WiFi interrupt or the
    // scheduler cannot stretch it.
    const rmt_symbol_word_t pulse = {
        .level0 = 1,
        .duration0 = width_us,
        .level1 = 0,
        .duration1 = 1,
    };
    const rmt_transmit_config_t tx_cfg = {.loop_count = 0, .flags.eot_level = 0};
    s_last_pulse_us = esp_timer_get_time();
    ESP_ERROR_CHECK(rmt_transmit(s_rmt, s_encoder, &pulse, sizeof(pulse), &tx_cfg));
    ESP_ERROR_CHECK(rmt_tx_wait_all_done(s_rmt, RMT_DONE_TIMEOUT_MS));
}

void panel_hw_pulse(shift_frame_t frame, uint32_t width_us)
{
    if (width_us > PANEL_PULSE_MAX_US) {
        ESP_LOGE(TAG, "pulse of %lu us clamped", (unsigned long)width_us);
        width_us = PANEL_PULSE_MAX_US;
    }

    int64_t wait_us = s_last_pulse_us + MIN_PULSE_PERIOD_US - esp_timer_get_time();
    if (wait_us > 0) {
        esp_rom_delay_us((uint32_t)wait_us);
    }

    // Address and select settle while both strobes are low, so no current flows
    // until the pulse, and a crash here leaves every coil off.
    set_lines(frame);
    esp_rom_delay_us(ADDR_SETTLE_US);

    // Exactly one polarity strobe fires per dot: ROW-HIGH for yellow, ROW-LOW for
    // black. The idle frame sets neither, so nothing is energised.
    if (frame.u3 & U3_ROW_HIGH_BIT) {
        route_rmt_to(PIN_ROW_HIGH);
        strobe(width_us);
    } else if (frame.u3 & U3_ROW_LOW_BIT) {
        route_rmt_to(PIN_ROW_LOW);
        strobe(width_us);
    }

    // Back to idle: deselect and clear the address.
    set_lines(flipdot_idle_frame());
}
